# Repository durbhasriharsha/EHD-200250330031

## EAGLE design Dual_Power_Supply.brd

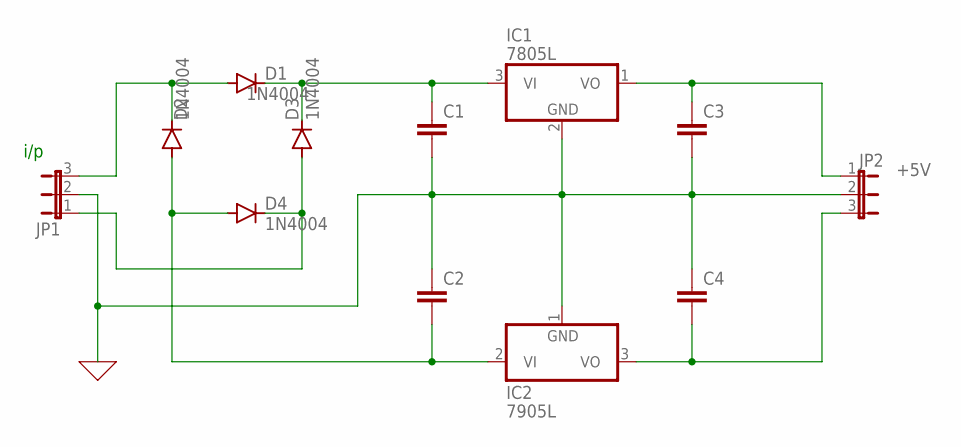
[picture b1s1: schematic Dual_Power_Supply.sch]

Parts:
C1, C2, C3, C4: C2,5-3; C2.5-3
D1, D2, D3, D4: 1N4004; DO41-10
IC1: 7805L; TO92
IC3: 7905L; TO92
JP1, JP2: JP2E; JP2

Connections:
0: C1.2, C2.1, C3.2, C4.1, IC1.2 (GND), IC3.1 (GND), JP1.2, JP2.2
unnamed: D1.A, D2.C, JP1.3
unnamed: C1.1, D1.C, D3.C, IC1.3 (VI)
unnamed: D3.A, D4.C, JP1.1
unnamed: C2.2, D2.A, D4.A, IC3.2 (VI)
unnamed: C4.2, IC3.3 (VO), JP2.3
unnamed: C3.1, IC1.1 (VO), JP2.1

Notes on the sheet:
+5V
7905L
IC2
i/p

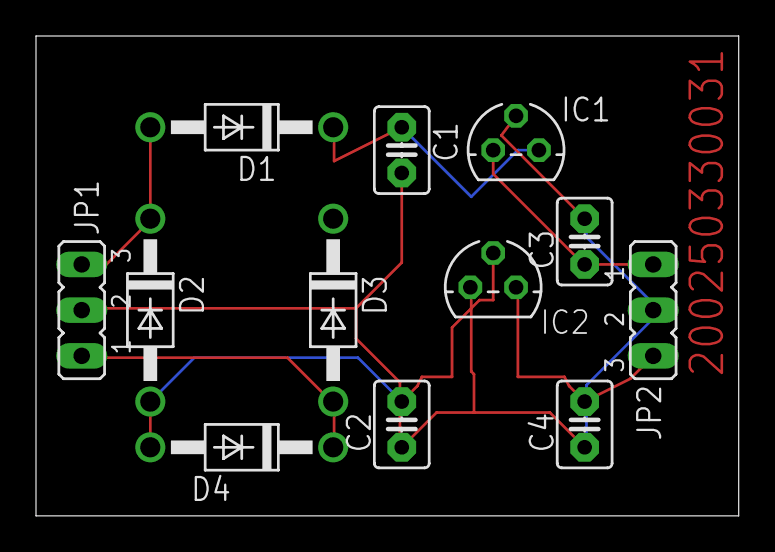
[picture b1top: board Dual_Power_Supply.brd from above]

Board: 2 copper layers, 39.0 x 26.7 mm, 12 parts (0 on the bottom side), 7 nets.

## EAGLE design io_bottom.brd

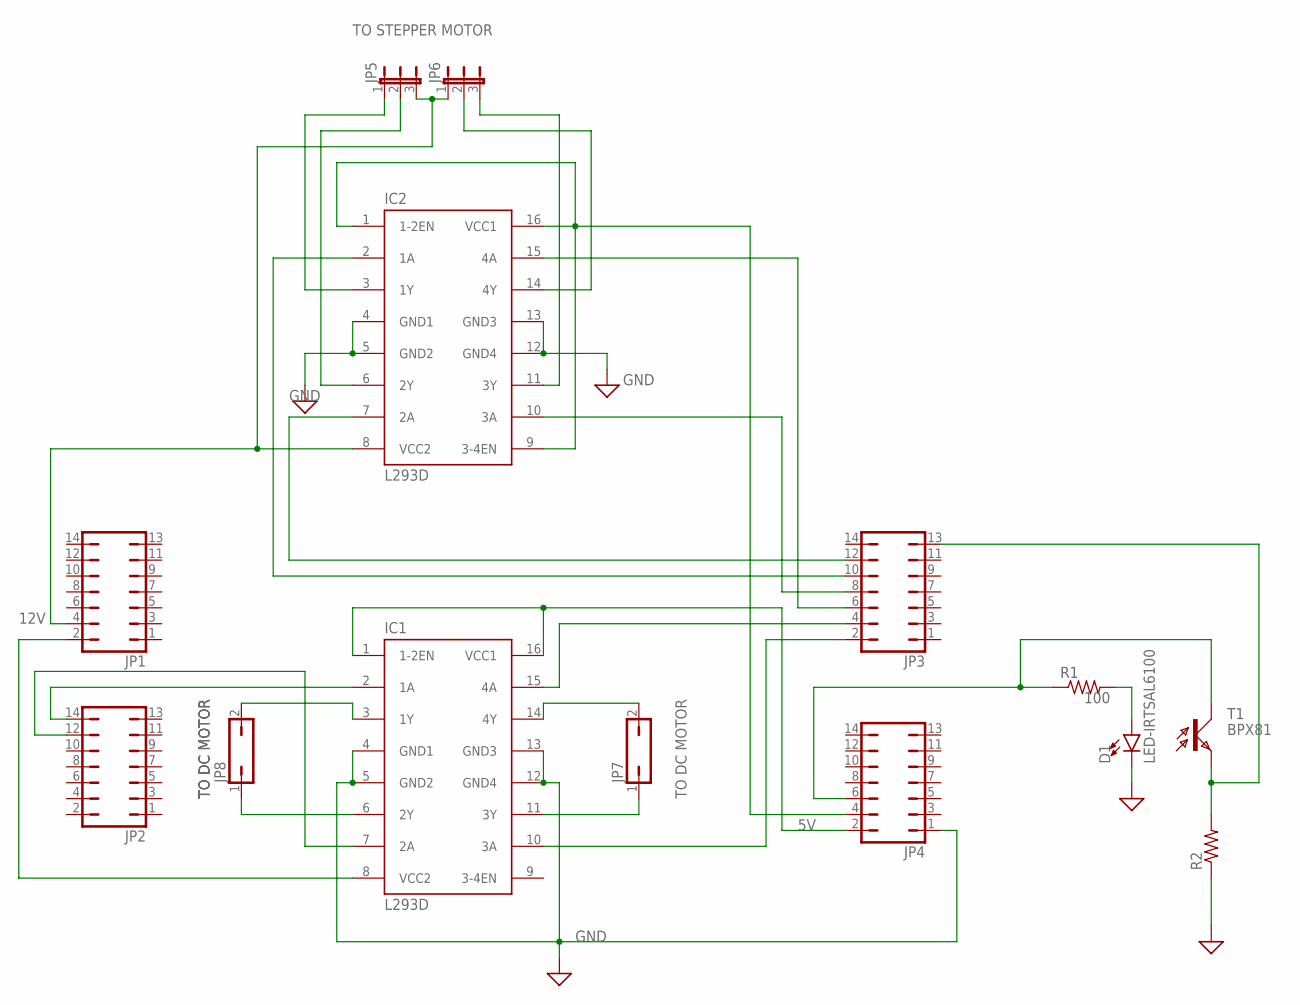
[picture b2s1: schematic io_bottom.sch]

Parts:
D1: LED-IRTSAL6100; LED_5MM
IC1, IC2: L293D; DIL16
JP1, JP2, JP3, JP4: JP7Q
JP5, JP6: JP2E; JP2
JP7, JP8: JP1Q; JP1
R1, R2: R-US_0204/2V; 0204V
T1: BPX81

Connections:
5V: IC1.8 (VCC2), JP1.2
GND: D1.K (C), IC1.4 (GND1), IC1.5 (GND2), IC1.12 (GND4), IC1.13 (GND3), IC2.4 (GND1), IC2.5 (GND2), IC2.12 (GND4), IC2.13 (GND3), JP4.1, R2.1
unnamed: IC1.3 (1Y), JP8.2
unnamed: IC1.6 (2Y), JP8.1
unnamed: IC1.11 (3Y), JP7.1
unnamed: IC1.14 (4Y), JP7.2
unnamed: IC1.2 (1A), JP2.14
unnamed: IC1.7 (2A), JP2.12
unnamed: IC1.1 (1-2EN), IC1.16 (VCC1), JP4.2
unnamed: IC1.15 (4A), JP3.4
unnamed: IC1.10 (3A), JP3.2
unnamed: IC2.15 (4A), JP3.6
unnamed: IC2.10 (3A), JP3.8
unnamed: IC2.2 (1A), JP3.10
unnamed: IC2.7 (2A), JP3.12
unnamed: IC2.1 (1-2EN), IC2.9 (3-4EN), IC2.16 (VCC1), JP4.4
unnamed: IC2.6 (2Y), JP5.2
unnamed: IC2.3 (1Y), JP5.1
unnamed: IC2.11 (3Y), JP6.3
unnamed: IC2.8 (VCC2), JP1.4, JP5.3, JP6.1
unnamed: IC2.14 (4Y), JP6.2
unnamed: D1.A, R1.2
unnamed: JP3.13, R2.2, T1.E
unnamed: JP4.6, R1.1, T1.C

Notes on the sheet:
12V
GND
TO STEPPER MOTOR
TO DC MOTOR
100

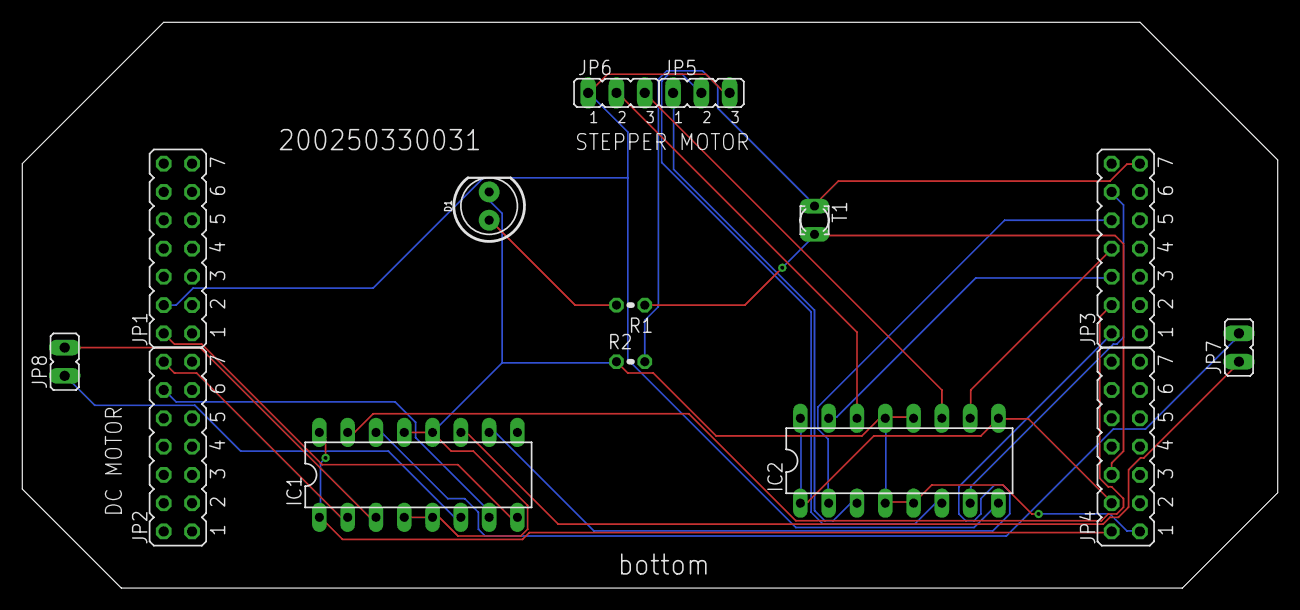
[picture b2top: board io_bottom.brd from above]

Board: 2 copper layers, 112.7 x 50.8 mm, 14 parts (0 on the bottom side), 24 nets.

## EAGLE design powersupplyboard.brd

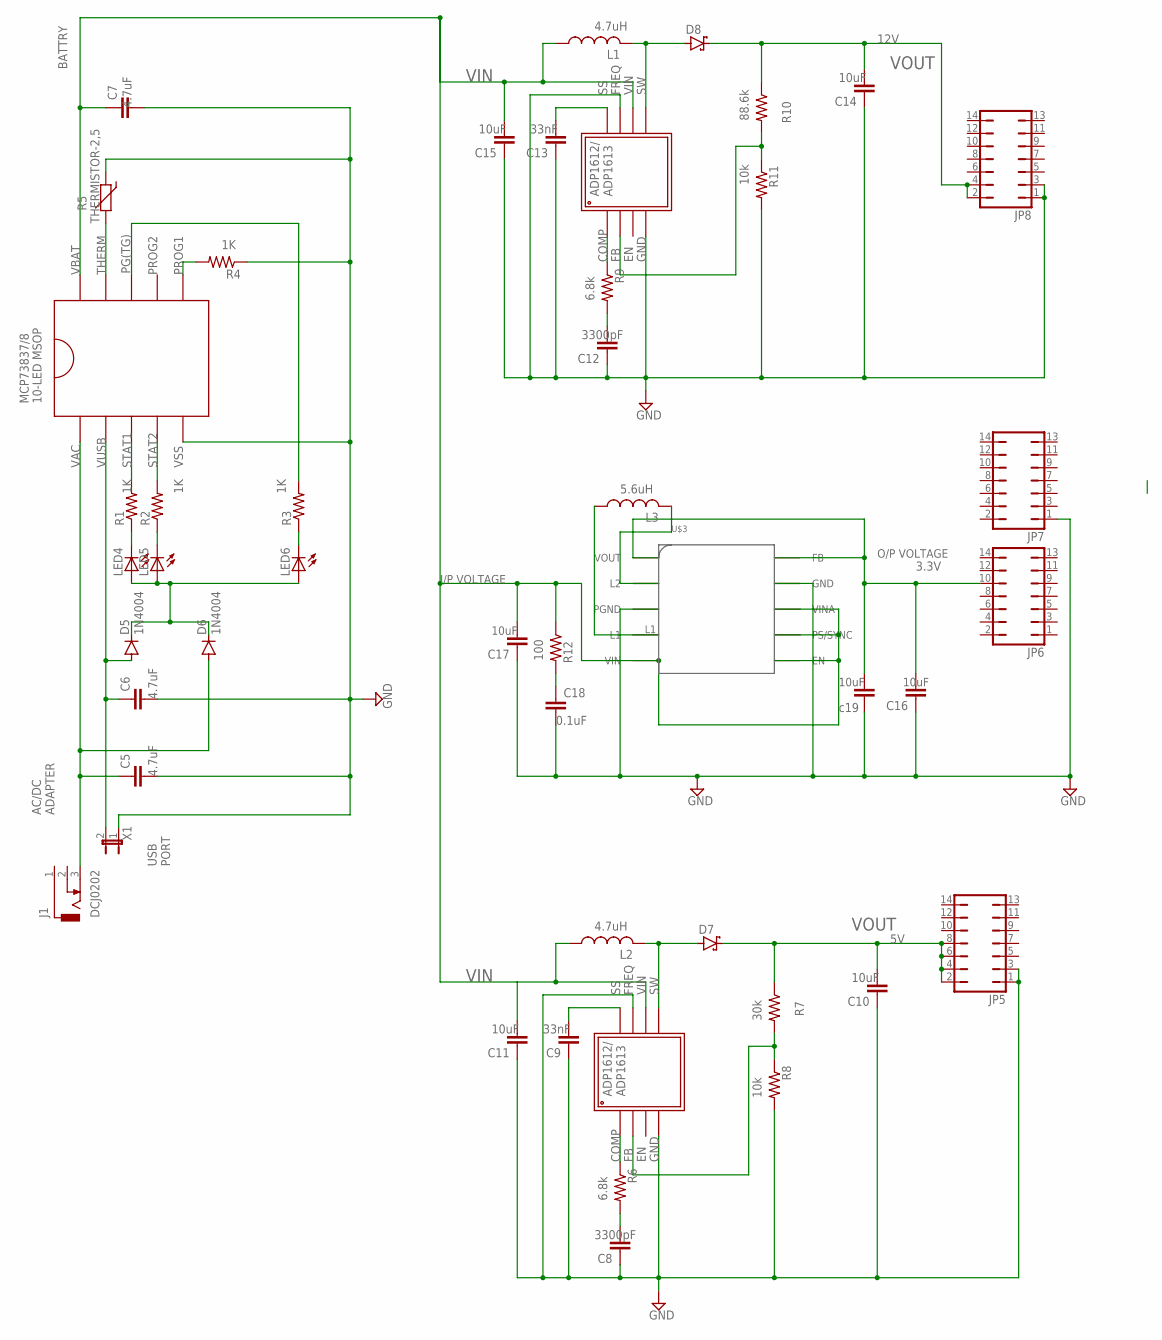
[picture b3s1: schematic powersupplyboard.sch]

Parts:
C1, C8, C9, C10, C11, C12, C13, C14, C15, C16, C17, C18: C2,5-3; C2.5-3
C5, C6, C7: C2.5/5; C2.5-5
D5, D6: 1N4004; DO41-10
D7, D8: SCHOTTKY-DIODEC4111-15; C4111-15
J1: DCJ0202
JP1: JP1E; JP1
JP5, JP6, JP7, JP8: JP7Q
L1, L2, L3: L-US0204/5; 0204/5
LED4, LED5, LED6: LED3MM
R1, R2, R3, R4, R6, R7, R8, R9, R10, R11, R12: R-US_0204/2V; 0204V
R5: THERMISTOR-2,5; RS-2,5
U$1, U$2: ADP1612
U$3: TPS63002
U$4: MCP73837/8

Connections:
GND: C1.1, C5.2, C6.2, C7.2, C8.1, C9.1, C10.1, C11.1, C12.1, C13.1, C14.1, C15.1, C16.1, C17.1, C18.2, JP1.1, JP5.1, JP5.3, JP7.1, JP8.1, JP8.3, R4.1, R5.1, R8.2, R11.2, U$1.P$4, U$1.P$6, U$2.P$4, U$2.P$6, U$3.GND, U$3.PGND, U$4.P$5
unnamed: C7.1, C11.2, C15.2, C17.2, L1.1, L2.1, R12.1, U$1.P$7, U$2.P$7, U$3.EN, U$3.PS/SYNC, U$3.VIN, U$3.VINA, U$4.P$10
unnamed: L3.1, U$3.L1
unnamed: C1.2, C16.2, JP6.10, U$3.FB, U$3.VOUT
unnamed: L3.2, U$3.L2
unnamed: C18.1, R12.2
unnamed: C5.1, D6.A, J1.3, U$4.P$1
unnamed: C10.2, D7.C, JP5.2, JP5.4, JP5.6, JP5.8, R7.1
unnamed: C14.2, D8.C, JP8.2, JP8.4, R10.1
unnamed: C6.1, D5.A, JP1.2, U$4.P$2
unnamed: D5.C, D6.C, LED4.A, LED5.A, LED6.A
unnamed: R4.2, U$4.P$6
unnamed: R5.2, U$4.P$9
unnamed: LED4.K (C), R1.1
unnamed: R1.2, U$4.P$3
unnamed: R2.2, U$4.P$4
unnamed: LED5.K (C), R2.1
unnamed: LED6.K (C), R3.1
unnamed: R3.2, U$4.P$8
unnamed: D7.A, L2.2, U$1.P$8
unnamed: R6.1, U$1.P$1
unnamed: C8.2, R6.2
unnamed: R7.2, R8.1, U$1.P$2
unnamed: C9.2, U$1.P$5
unnamed: D8.A, L1.2, U$2.P$8
unnamed: R9.1, U$2.P$1
unnamed: C12.2, R9.2
unnamed: R10.2, R11.1, U$2.P$2
unnamed: C13.2, U$2.P$5

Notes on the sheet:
AC/DC ADAPTER
USB PORT
BATTRY
VIN
VOUT
10uF
30k
10k
4.7uH
33nF
6.8k
3300pF
88.6k
I/P VOLTAGE
O/P VOLTAGE
5.6uH
c19
3.3V
12V
100
0.1uF
4.7uF

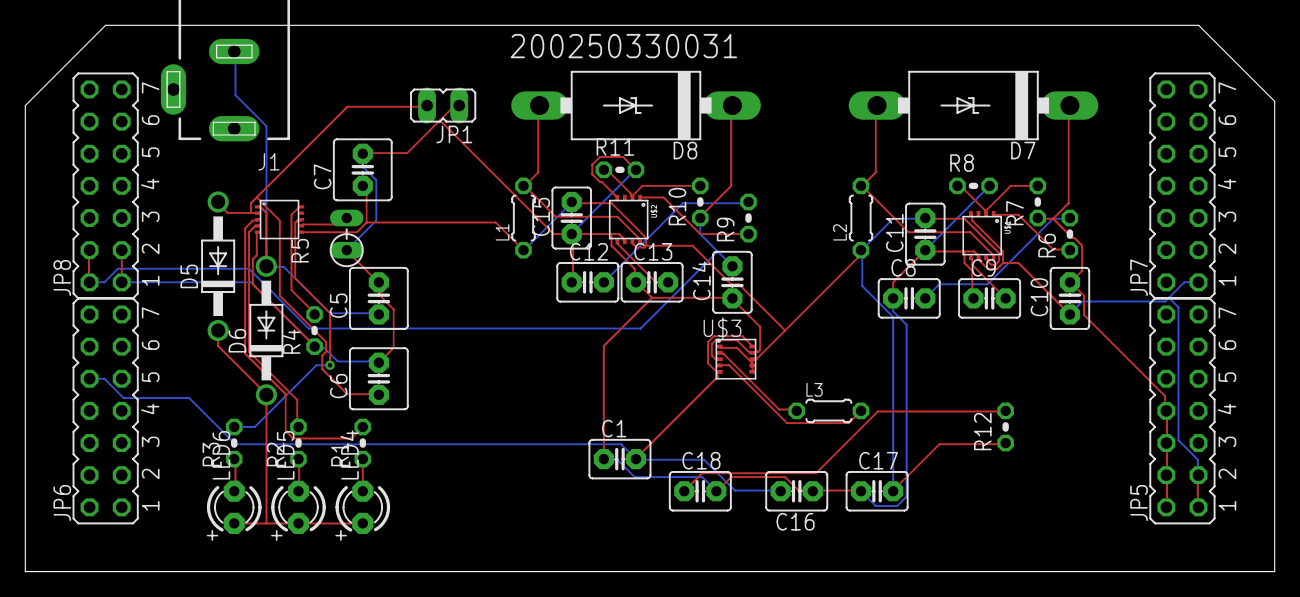
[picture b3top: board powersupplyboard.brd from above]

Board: 2 copper layers, 98.7 x 43.2 mm, 47 parts (0 on the bottom side), 29 nets.

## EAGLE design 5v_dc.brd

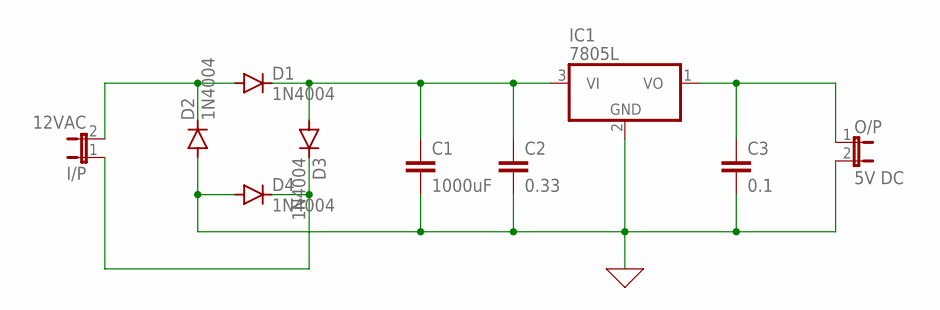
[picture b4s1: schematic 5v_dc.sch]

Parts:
C1: 1000uF; C2.5-3
C2: 0.33; C2.5-3
C3: 0.1; C2.5-3
D1, D2, D3, D4: 1N4004; DO41-10
I/P: 12VAC; JP1
IC1: 7805L; TO92
O/P: 5V DC; JP1

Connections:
0: C1.2, C2.2, C3.2, D2.A, D4.A, IC1.2 (GND), O/P.2
unnamed: D1.A, D2.C, I/P.2
unnamed: C3.1, IC1.1 (VO), O/P.1
unnamed: D3.C, D4.C, I/P.1
unnamed: C1.1, C2.1, D1.C, D3.A, IC1.3 (VI)

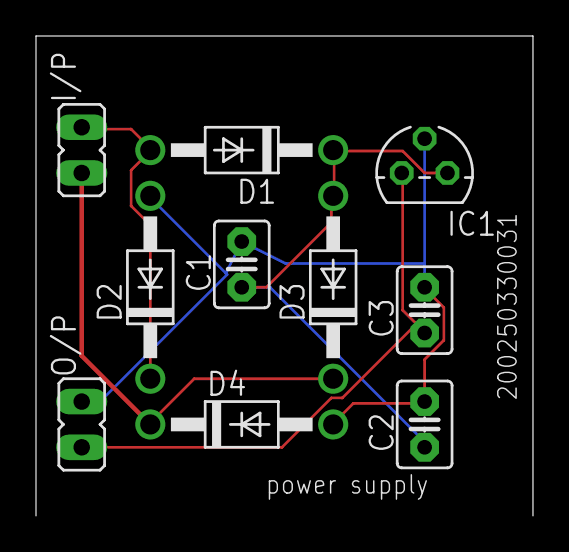
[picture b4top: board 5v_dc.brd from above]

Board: 2 copper layers, 27.6 x 26.7 mm, 10 parts (0 on the bottom side), 5 nets.

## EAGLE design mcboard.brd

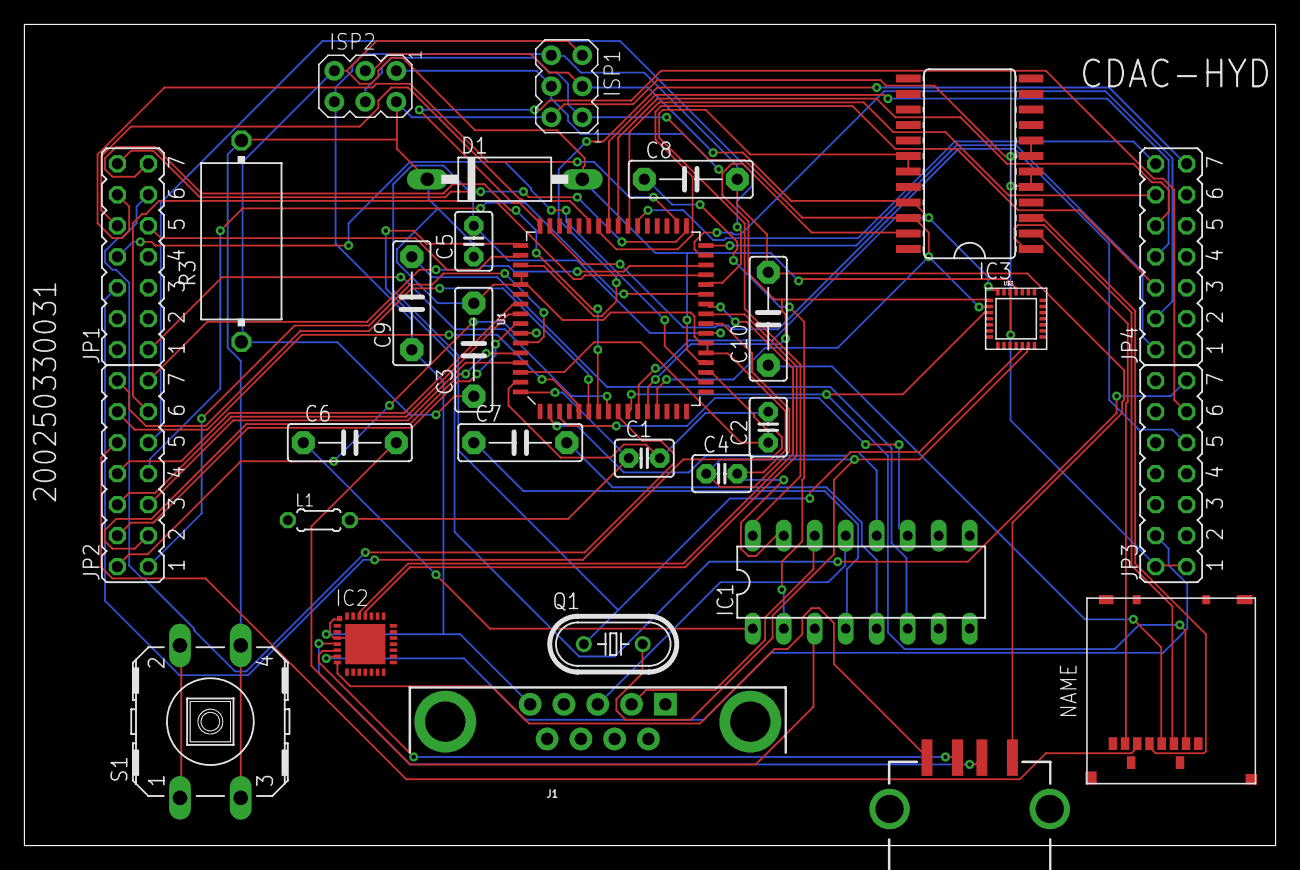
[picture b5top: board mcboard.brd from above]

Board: 2 copper layers, 102.5 x 67.3 mm, 29 parts (0 on the bottom side), 68 nets.

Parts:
C1, C2, C4, C5: C2.5-3
C3, C6, C7, C8, C9, C10: C7.5B3
D1: EGP20A; DO15-12
IC1: MAX232; DIL16
IC2: CP2101; MLP28
IC3: 74AC11244D; SO24W
ISP1, ISP2: AVRISP-6; AVRISP
J1: DB9
J2: USB_A_SMT_FEMALE; USB-A-S-SILK-FEMALE
JP1, JP2, JP3, JP4: JP7Q
L1: 0204/5
Q1: HC49U-V
R3: VTA55
S1: RACON12
U1: ATMEGA128-SMD; TQFP64_14X14MM
U$1: SD-CARD
U$2: CC2520

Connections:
3.3V: C10.1, U$1.P$4
5V: C3.2, C4.2, C5.1, D1.C, IC1.15, IC3.5, IC3.6, IC3.7, IC3.8, ISP1.2, ISP2.2, JP3.1, JP3.2, R3.2, S1.3, S1.4, U1.21, U1.22, U1.52, U1.53, U$2.P$26
GND: C8.2, C9.1, C10.2, IC2.3, IC2.EXP, IC2.M, ISP1.6, ISP2.6, J1.5, J2.GND
unnamed: C2.1, U1.62
unnamed: C1.2, C2.2, U1.63
unnamed: C1.1, L1.2, U1.64
unnamed: S1.1, S1.2
unnamed: C6.1, IC1.1
unnamed: U1.10, U$1.P$2, U$2.P$3
unnamed: C4.1, Q1.2, U1.24, U$2.P$13
unnamed: C5.2, Q1.1, U1.23, U$2.P$12
unnamed: IC3.22, ISP1.1, ISP2.4, U1.13, U$2.P$2
unnamed: IC3.23, ISP1.4, ISP2.1, U1.12, U$2.P$1
unnamed: IC3.21, ISP1.3, ISP2.3, U1.11, U$2.P$28
unnamed: C9.2, IC1.6
unnamed: C8.1, IC1.2
unnamed: C7.1, IC1.4
unnamed: C6.2, IC1.3
unnamed: C7.2, IC1.5
unnamed: IC2.25, U1.25
unnamed: IC1.11, U1.3
unnamed: IC1.12, U1.2
unnamed: IC3.3, U$1.P$5
unnamed: JP2.5, U1.61
unnamed: IC2.5, J2.D-
unnamed: JP2.3, U1.60
unnamed: IC2.4, J2.D+
unnamed: IC2.7, J2.VBUS
unnamed: IC1.14, J1.2
unnamed: IC1.13, J1.3
unnamed: C3.1, D1.A, ISP1.5, ISP2.5, R3.1, U1.20, U$2.P$25
unnamed: IC2.26, U1.26
unnamed: IC3.1, U$1.P$3
unnamed: IC3.2, U$1.P$7
unnamed: JP2.12, U1.5
unnamed: JP2.14, U1.6
unnamed: JP4.2, U1.32
unnamed: JP4.4, U1.31
unnamed: JP4.12, U1.39
unnamed: JP4.10, U1.40
unnamed: JP4.8, U1.41
unnamed: JP4.6, U1.42
unnamed: JP4.13, U1.51
unnamed: JP1.11, U1.9
unnamed: JP1.1, U1.8
unnamed: JP1.13, U1.7
unnamed: JP1.9, U1.50
unnamed: JP4.14, U1.38
unnamed: JP1.14, U1.33
unnamed: JP1.12, U1.34
unnamed: JP1.10, U1.43
unnamed: JP1.8, U1.18
unnamed: JP1.6, U1.19
unnamed: JP2.13, U1.30
unnamed: JP2.11, U1.29
unnamed: JP2.9, U1.28
unnamed: JP2.7, U1.27
unnamed: JP2.1, U1.59
unnamed: JP2.2, U1.58
unnamed: JP2.4, U1.57
unnamed: JP2.6, U1.56
unnamed: JP2.8, U1.55
unnamed: JP2.10, U$1.P$6
unnamed: JP3.13, U1.49
unnamed: JP3.11, U1.48
unnamed: JP3.9, U1.47
unnamed: IC2.6, JP3.4
VCC: IC1.16, IC3.18, IC3.19

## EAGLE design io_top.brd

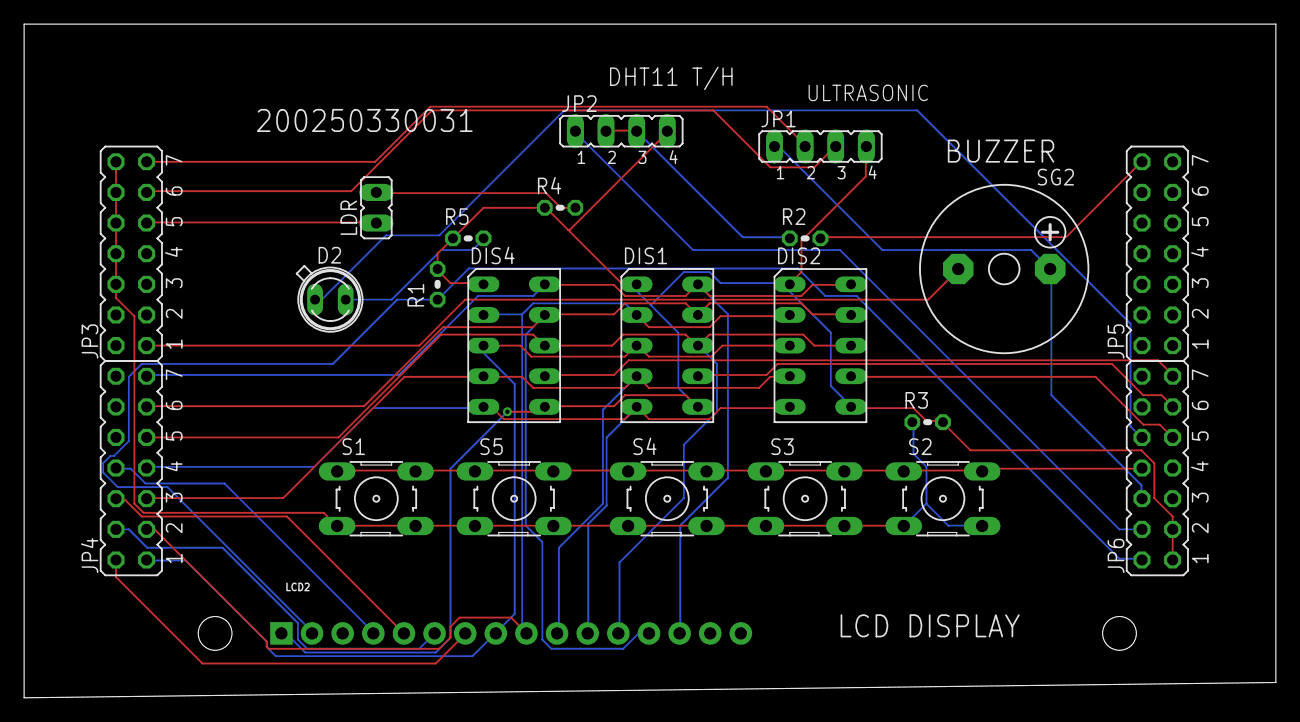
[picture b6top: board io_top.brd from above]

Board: 2 copper layers, 103.8 x 55.9 mm, 23 parts (0 on the bottom side), 29 nets.

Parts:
D2: SFH482
DIS1, DIS2, DIS4: HD-A103; HDSP-A
JP1, JP2: JP4
JP3, JP4, JP5, JP6: JP7Q
LCD2: LCD-16X2NOSILK; LCD-16X2_NOSILK
LDR: JP1
R1, R2, R3, R4, R5: 0204V
S1, S2, S3, S4, S5: B3F-10XX
SG2: F/CM12P

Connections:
5V: JP1.1, JP6.6, SG2.+
GND: DIS1.1, DIS1.6, DIS2.1, DIS2.6, DIS4.1, DIS4.6, JP1.4, JP2.4, JP6.1, JP6.3, LCD2.1, R1.2, R3.2, R4.1, R5.1
unnamed: JP3.1, SG2.-
unnamed: JP2.2, JP2.3, R2.1
unnamed: DIS1.3, DIS2.3, DIS4.3, JP4.1, LCD2.8
unnamed: DIS1.2, DIS2.2, DIS4.2, JP4.3, LCD2.9
unnamed: DIS1.4, DIS2.4, DIS4.4, JP4.5, LCD2.10
unnamed: DIS1.5, DIS2.5, DIS4.5, JP4.7, LCD2.11
unnamed: DIS1.8, DIS2.8, DIS4.8, JP4.9, LCD2.12
unnamed: DIS1.9, DIS2.9, DIS4.9, JP4.11, LCD2.13
unnamed: DIS1.10, DIS2.10, DIS4.10, JP4.13, LCD2.14
unnamed: JP4.2, LCD2.7
unnamed: JP6.2, LCD2.2, R1.1
unnamed: JP1.3, JP3.11
unnamed: JP4.4, LCD2.6
unnamed: JP4.6, LCD2.5
unnamed: JP4.8, LCD2.4
unnamed: JP3.6, JP3.8, JP3.10, JP3.12, JP3.14, R3.1, S1.3, S1.4, S2.3, S2.4, S3.3, S3.4, S4.3, S4.4, S5.3, S5.4
unnamed: JP1.2, JP3.13
unnamed: JP5.14, R2.2
unnamed: JP3.9, LDR.1
unnamed: LDR.2, R4.2
unnamed: JP2.1, JP6.4
unnamed: JP6.8, S1.1, S1.2, S2.1, S2.2, S3.1, S3.2, S4.1, S4.2, S5.1, S5.2
unnamed: D2.K, R5.2
unnamed: D2.A, JP6.10
unnamed: DIS4.7, JP6.13
unnamed: DIS1.7, JP6.11
unnamed: DIS2.7, JP6.9

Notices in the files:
parts and their libraries:
SparkFun-LED: Licensing: Creative Commons ShareAlike 4.0 International - https://creativecommons.org/licenses/by-sa/4.0
